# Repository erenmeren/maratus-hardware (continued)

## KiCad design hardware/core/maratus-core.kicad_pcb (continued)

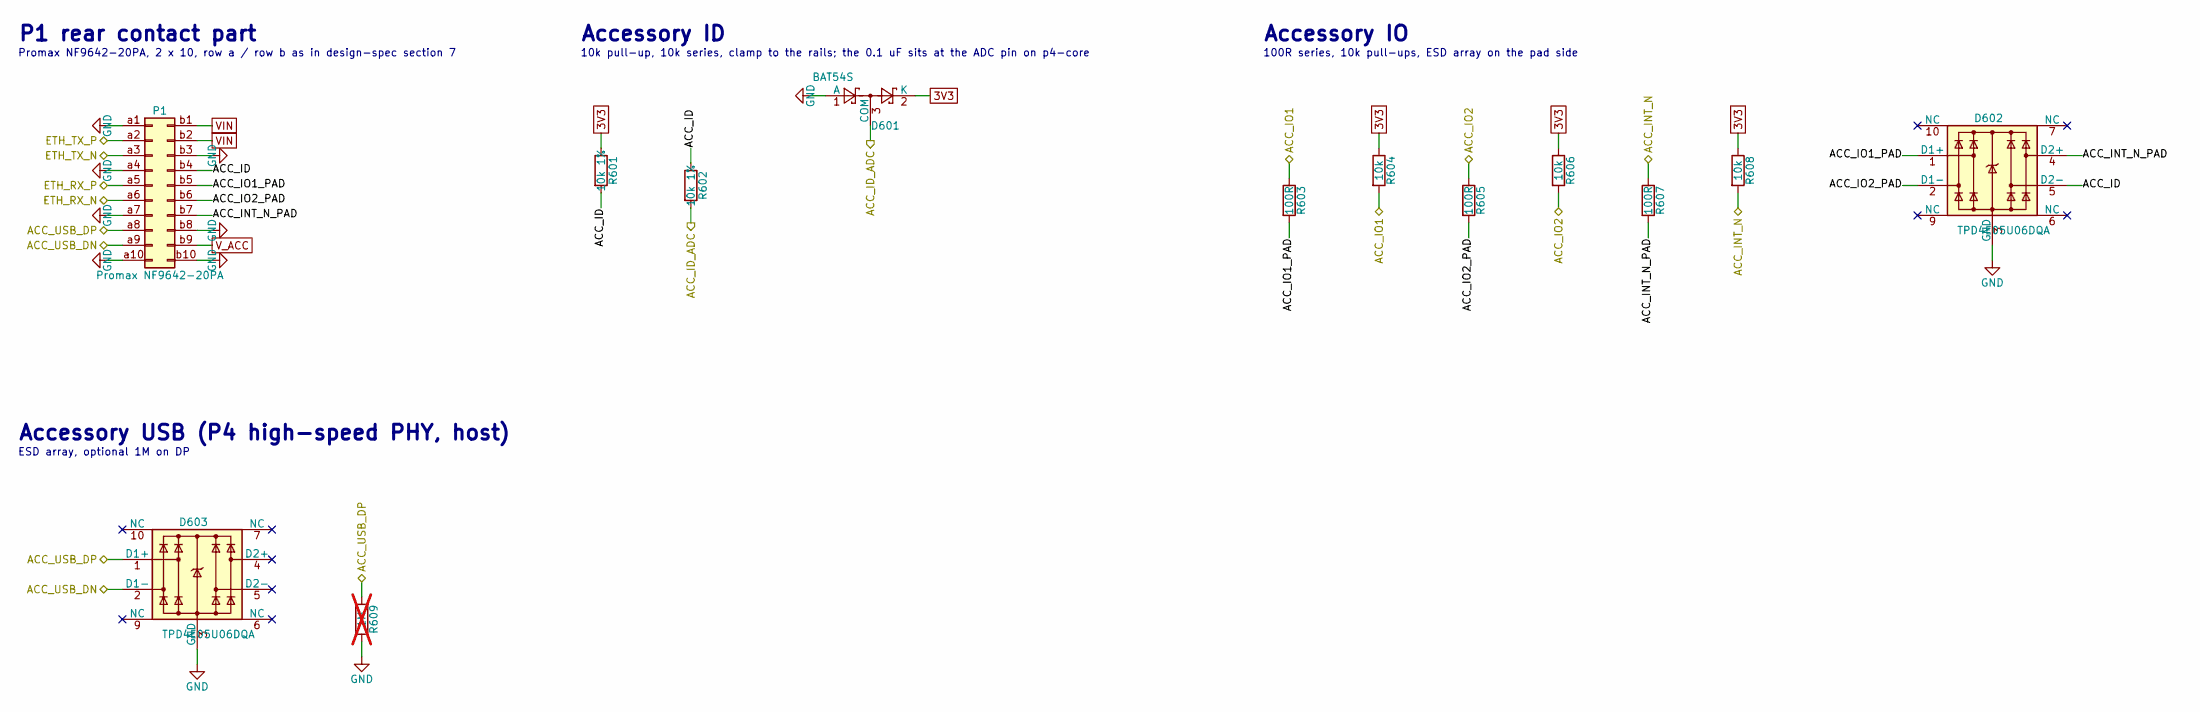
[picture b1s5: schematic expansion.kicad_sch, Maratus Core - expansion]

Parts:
D601: BAT54S; SOT-23
D602, D603: TPD4E05U06DQA; USON-10_2.5x1.0mm_P0.5mm
P1: Promax NF9642-20PA; Promax_NF9642-20PA
R601, R602: 10k 1%; R_0402_1005Metric
R603, R605, R607: 100R; R_0402_1005Metric
R604, R606, R608: 10k; R_0402_1005Metric
R609: 1M; R_0402_1005Metric; not fitted

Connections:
3V3: D601.2 (K), R601.1, R604.1, R606.1, R608.1; also elsewhere on the board
/ACC_ID_ADC: D601.3 (COM), R602.2; also elsewhere on the board
/ACC_INT_N: R607.1, R608.2; also elsewhere on the board
/ACC_IO1: R603.1, R604.2; also elsewhere on the board
/ACC_IO2: R605.1, R606.2; also elsewhere on the board
/ACC_USB_DN: D603.2 (D1-), P1.a9; also elsewhere on the board
/ACC_USB_DP: D603.1 (D1+), P1.a8, R609.1; also elsewhere on the board
/ETH_RX_N: P1.a6; also elsewhere on the board
/ETH_RX_P: P1.a5; also elsewhere on the board
/ETH_TX_N: P1.a3; also elsewhere on the board
/ETH_TX_P: P1.a2; also elsewhere on the board
/expansion/ACC_ID: D602.5 (D2-), P1.b4, R601.2, R602.1
/expansion/ACC_INT_N_PAD: D602.4 (D2+), P1.b7, R607.2
/expansion/ACC_IO1_PAD: D602.1 (D1+), P1.b5, R603.2
/expansion/ACC_IO2_PAD: D602.2 (D1-), P1.b6, R605.2
GND: D601.1 (A), D602.3 (GND), D602.8 (GND), D603.3 (GND), D603.8 (GND), P1.a1, P1.a4, P1.a7, P1.a10, P1.b3, P1.b8, P1.b10, R609.2; also elsewhere on the board
VIN: P1.b1, P1.b2; also elsewhere on the board
V_ACC: P1.b9; also elsewhere on the board

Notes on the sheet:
Accessory USB (P4 high-speed PHY, host)
Accessory ID
P1 rear contact part
Promax NF9642-20PA, 2 x 10, row a / row b as in design-spec section 7
Accessory IO
100R series, 10k pull-ups, ESD array on the pad side
10k pull-up, 10k series, clamp to the rails; the 0.1 uF sits at the ADC pin on p4-core
ESD array, optional 1M on DP

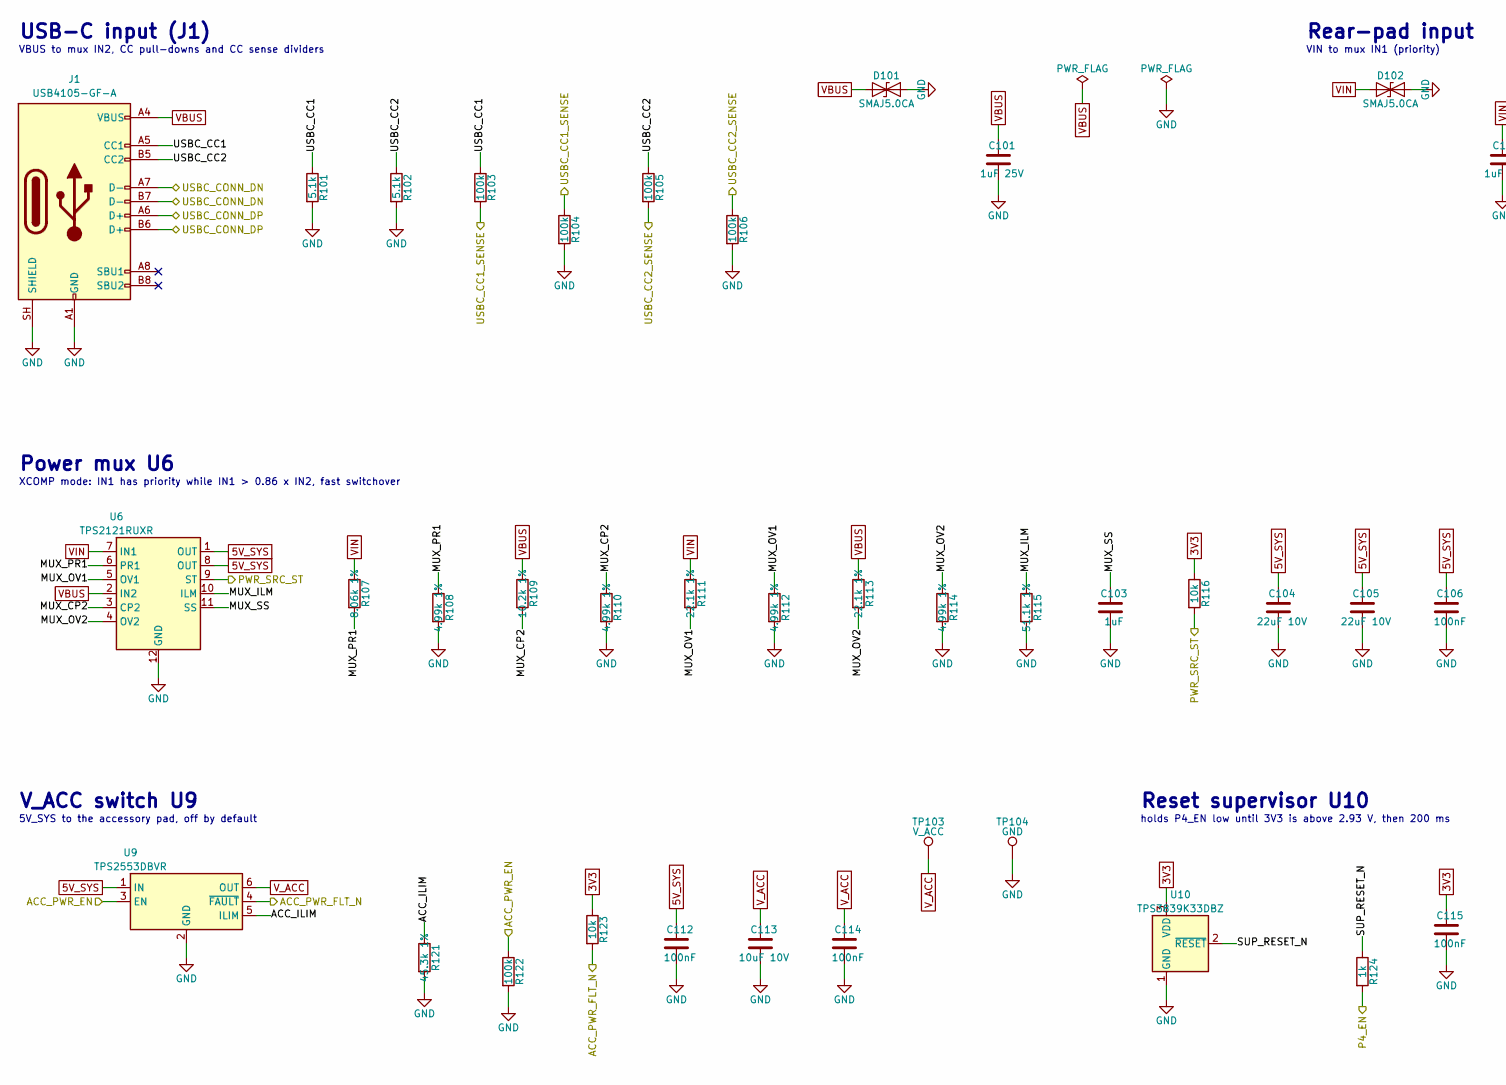
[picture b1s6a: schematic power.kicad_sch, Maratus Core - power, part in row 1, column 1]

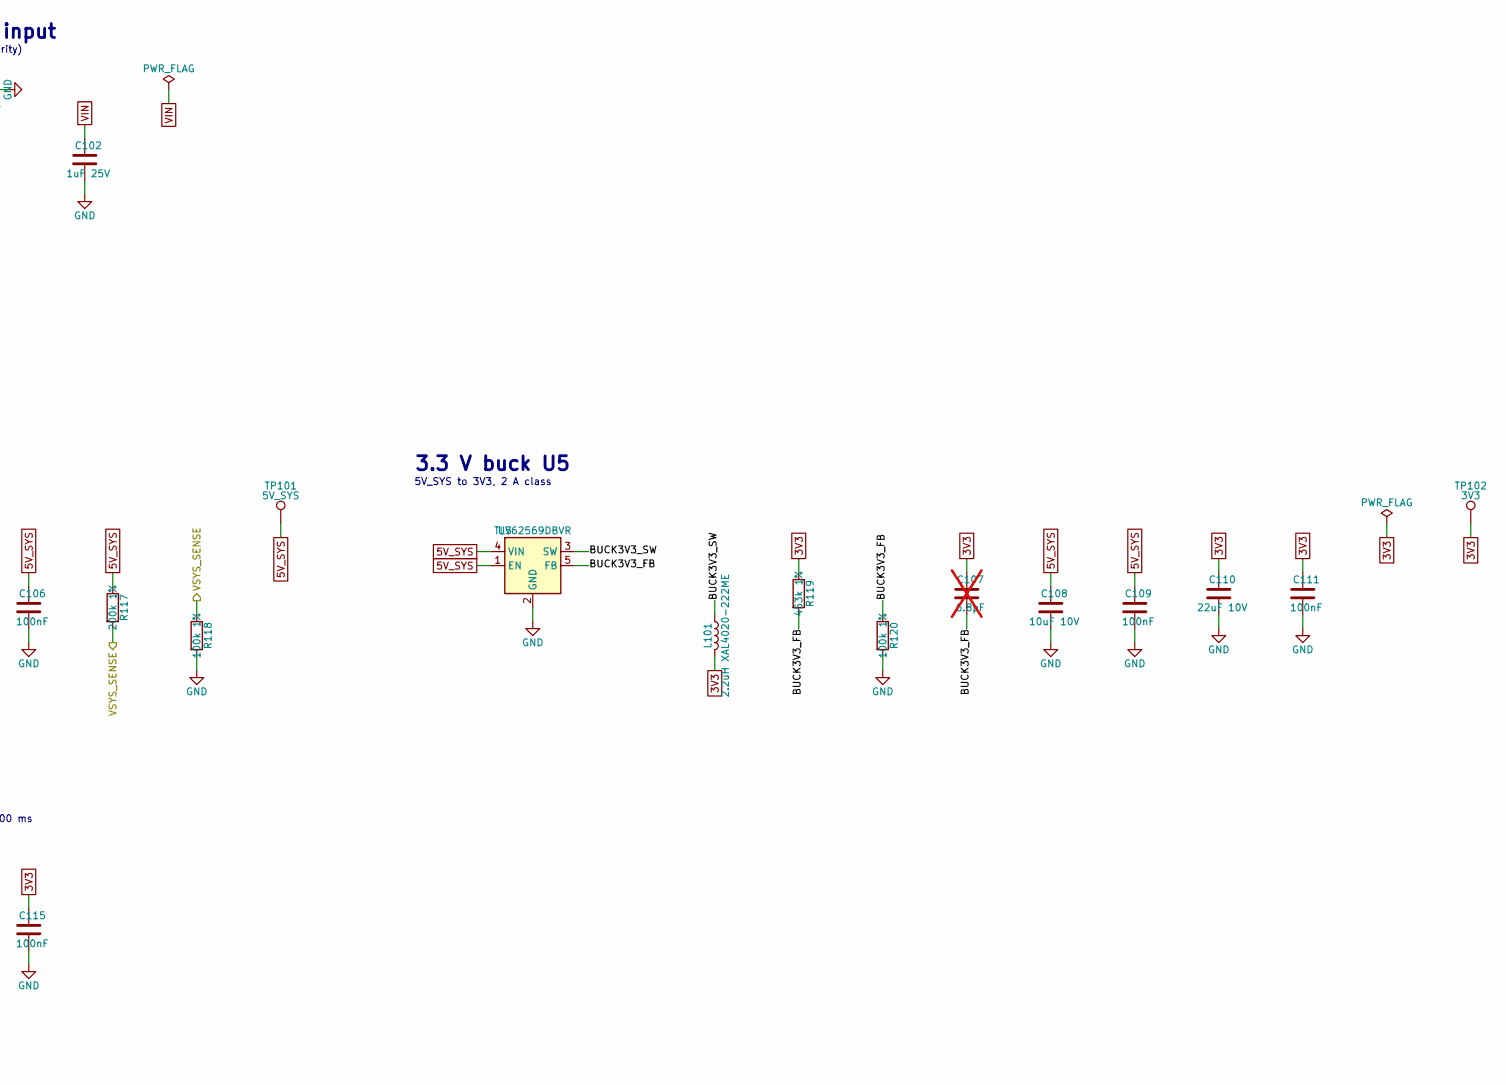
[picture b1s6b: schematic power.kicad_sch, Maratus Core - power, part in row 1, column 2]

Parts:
C101, C102: 1uF 25V; C_0603_1608Metric
C103: 1uF; C_0402_1005Metric
C104, C105, C110: 22uF 10V; C_0805_2012Metric
C106, C109, C111, C112, C114, C115: 100nF; C_0402_1005Metric
C107: 6.8pF; C_0402_1005Metric; not fitted
C108, C113: 10uF 10V; C_0805_2012Metric
D101, D102: SMAJ5.0CA; D_SMA
J1: USB4105-GF-A; USB_C_Receptacle_GCT_USB4105-xx-A_16P_TopMnt_Horizontal
L101: 2.2uH XAL4020-222ME; L_Coilcraft_XAL4020-XXX
R101, R102: 5.1k; R_0402_1005Metric
R103, R104, R105, R106, R122: 100k; R_0402_1005Metric
R107: 8.06k 1%; R_0402_1005Metric
R108, R110, R112, R114: 4.99k 1%; R_0402_1005Metric
R109: 10.2k 1%; R_0402_1005Metric
R111, R113: 22.1k 1%; R_0402_1005Metric
R115: 51.1k 1%; R_0402_1005Metric
R116, R123: 10k; R_0402_1005Metric
R117: 200k 1%; R_0402_1005Metric
R118, R120: 100k 1%; R_0402_1005Metric
R119: 453k 1%; R_0402_1005Metric
R121: 45.3k 1%; R_0402_1005Metric
R124: 1k; R_0402_1005Metric
TP101: 5V_SYS; TestPoint_Pad_D1.0mm
TP102: 3V3; TestPoint_Pad_D1.0mm
TP103: V_ACC; TestPoint_Pad_D1.0mm
TP104: GND; TestPoint_Pad_D1.0mm
U5: TLV62569DBVR; SOT-23-5
U6: TPS2121RUXR; Texas_VQFN-HR-12_2x2.5mm_P0.5mm
U9: TPS2553DBVR; SOT-23-6
U10: TPS3839K33DBZ; SOT-23

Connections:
3V3: C107.1, C110.1, C111.1, C115.1, L101.2, R116.1, R119.1, R123.1, TP102.1, U10.3 (VDD); also elsewhere on the board
5V_SYS: C104.1, C105.1, C106.1, C108.1, C109.1, C112.1, R117.1, TP101.1, U5.1 (EN), U5.4 (VIN), U6.1 (OUT), U6.8 (OUT), U9.1 (IN); also elsewhere on the board
/ACC_PWR_EN: R122.1, U9.3 (EN); also elsewhere on the board
/ACC_PWR_FLT_N: R123.2, U9.4 (~FAULT); also elsewhere on the board
/P4_EN: R124.2; also elsewhere on the board
/PWR_SRC_ST: R116.2, U6.9 (ST); also elsewhere on the board
/USBC_CC1_SENSE: R103.2, R104.1; also elsewhere on the board
/USBC_CC2_SENSE: R105.2, R106.1; also elsewhere on the board
/USBC_CONN_DN: J1.A7 (D-), J1.B7 (D-); also elsewhere on the board
/USBC_CONN_DP: J1.A6 (D+), J1.B6 (D+); also elsewhere on the board
/VSYS_SENSE: R117.2, R118.1; also elsewhere on the board
/power/ACC_ILIM: R121.1, U9.5 (ILIM)
/power/BUCK3V3_FB: C107.2, R119.2, R120.1, U5.5 (FB)
/power/BUCK3V3_SW: L101.1, U5.3 (SW)
/power/MUX_CP2: R109.2, R110.1, U6.3 (CP2)
/power/MUX_ILM: R115.1, U6.10 (ILM)
/power/MUX_OV1: R111.2, R112.1, U6.5 (OV1)
/power/MUX_OV2: R113.2, R114.1, U6.4 (OV2)
/power/MUX_PR1: R107.2, R108.1, U6.6 (PR1)
/power/MUX_SS: C103.1, U6.11 (SS)
/power/SUP_RESET_N: R124.1, U10.2 (~RESET)
/power/USBC_CC1: J1.A5 (CC1), R101.1, R103.1
/power/USBC_CC2: J1.B5 (CC2), R102.1, R105.1
GND: C101.2, C102.2, C103.2, C104.2, C105.2, C106.2, C108.2, C109.2, C110.2, C111.2, C112.2, C113.2, C114.2, C115.2, D101.2 (A2), D102.2 (A2), J1.A1 (GND), J1.A12 (GND), J1.B1 (GND), J1.B12 (GND), J1.SH (SHIELD), R101.2, R102.2, R104.2, R106.2, R108.2, R110.2, R112.2, R114.2, R115.2, R118.2, R120.2, R121.2, R122.2, TP104.1, U5.2 (GND), U6.12 (GND), U9.2 (GND), U10.1 (GND); also elsewhere on the board
VBUS: C101.1, D101.1 (A1), J1.A4 (VBUS), J1.A9 (VBUS), J1.B4 (VBUS), J1.B9 (VBUS), R109.1, R113.1, U6.2 (IN2); also elsewhere on the board
VIN: C102.1, D102.1 (A1), R107.1, R111.1, U6.7 (IN1); also elsewhere on the board
V_ACC: C113.1, C114.1, TP103.1, U9.6 (OUT); also elsewhere on the board

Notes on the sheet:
V_ACC switch U9
5V_SYS to 3V3, 2 A class
3.3 V buck U5
Rear-pad input
5V_SYS to the accessory pad, off by default
VBUS to mux IN2, CC pull-downs and CC sense dividers
USB-C input (J1)
XCOMP mode: IN1 has priority while IN1 > 0.86 x IN2, fast switchover
holds P4_EN low until 3V3 is above 2.93 V, then 200 ms
VIN to mux IN1 (priority)
Power mux U6
Reset supervisor U10

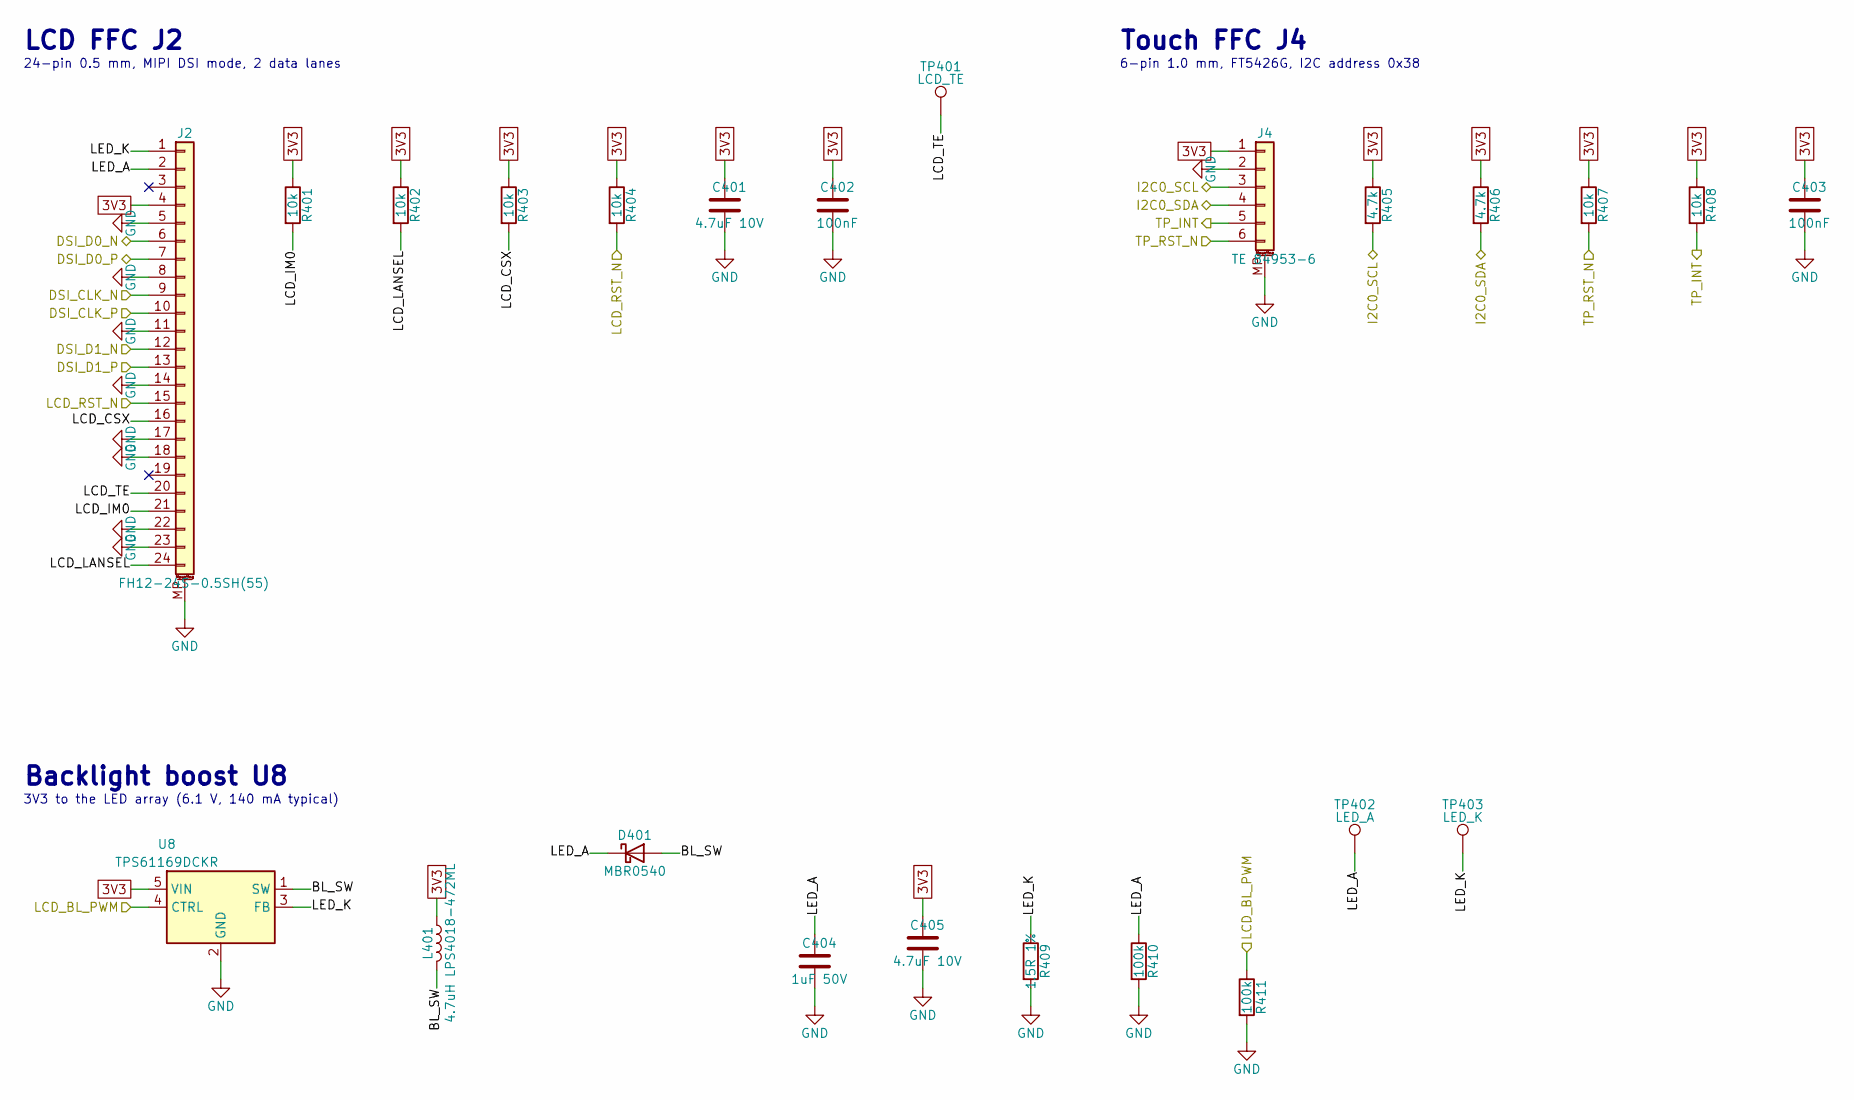
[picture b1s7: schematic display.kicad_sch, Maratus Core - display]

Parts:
C401, C405: 4.7uF 10V; C_0603_1608Metric
C402, C403: 100nF; C_0402_1005Metric
C404: 1uF 50V; C_0805_2012Metric
D401: MBR0540; D_SOD-123
J2: FH12-24S-0.5SH(55); Hirose_FH12-24S-0.5SH_1x24-1MP_P0.50mm_Horizontal
J4: TE 84953-6; TE_84953-6_1x06-1MP_P1.0mm_Horizontal
L401: 4.7uH LPS4018-472ML; L_Coilcraft_LPS4018
R401, R402, R403, R404, R407, R408: 10k; R_0402_1005Metric
R405, R406: 4.7k; R_0402_1005Metric
R409: 1.5R 1%; R_0603_1608Metric
R410, R411: 100k; R_0402_1005Metric
TP401: LCD_TE; TestPoint_Pad_D1.0mm
TP402: LED_A; TestPoint_Pad_D1.0mm
TP403: LED_K; TestPoint_Pad_D1.0mm
U8: TPS61169DCKR; SOT-353_SC-70-5

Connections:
3V3: C401.1, C402.1, C403.1, C405.1, J2.4, J4.1, L401.1, R401.1, R402.1, R403.1, R404.1, R405.1, R406.1, R407.1, R408.1, U8.5 (VIN); also elsewhere on the board
/DSI_CLK_N: J2.9; also elsewhere on the board
/DSI_CLK_P: J2.10; also elsewhere on the board
/DSI_D0_N: J2.6; also elsewhere on the board
/DSI_D0_P: J2.7; also elsewhere on the board
/DSI_D1_N: J2.12; also elsewhere on the board
/DSI_D1_P: J2.13; also elsewhere on the board
/I2C0_SCL: J4.3, R405.2; also elsewhere on the board
/I2C0_SDA: J4.4, R406.2; also elsewhere on the board
/LCD_BL_PWM: R411.1, U8.4 (CTRL); also elsewhere on the board
/LCD_RST_N: J2.15, R404.2; also elsewhere on the board
/TP_INT: J4.5, R408.2; also elsewhere on the board
/TP_RST_N: J4.6, R407.2; also elsewhere on the board
/display/BL_SW: D401.2 (A), L401.2, U8.1 (SW)
/display/LCD_CSX: J2.16, R403.2
/display/LCD_IM0: J2.21, R401.2
/display/LCD_LANSEL: J2.24, R402.2
/display/LCD_TE: J2.20, TP401.1
/display/LED_A: C404.1, D401.1 (K), J2.2, R410.1, TP402.1
/display/LED_K: J2.1, R409.1, TP403.1, U8.3 (FB)
GND: C401.2, C402.2, C403.2, C404.2, C405.2, J2.5, J2.8, J2.11, J2.14, J2.17, J2.18, J2.22, J2.23, J2.MP (MountPin), J4.2, J4.MP (MountPin), R409.2, R410.2, R411.2, U8.2 (GND); also elsewhere on the board

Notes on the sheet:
24-pin 0.5 mm, MIPI DSI mode, 2 data lanes
3V3 to the LED array (6.1 V, 140 mA typical)
6-pin 1.0 mm, FT5426G, I2C address 0x38
LCD FFC J2
Touch FFC J4
Backlight boost U8

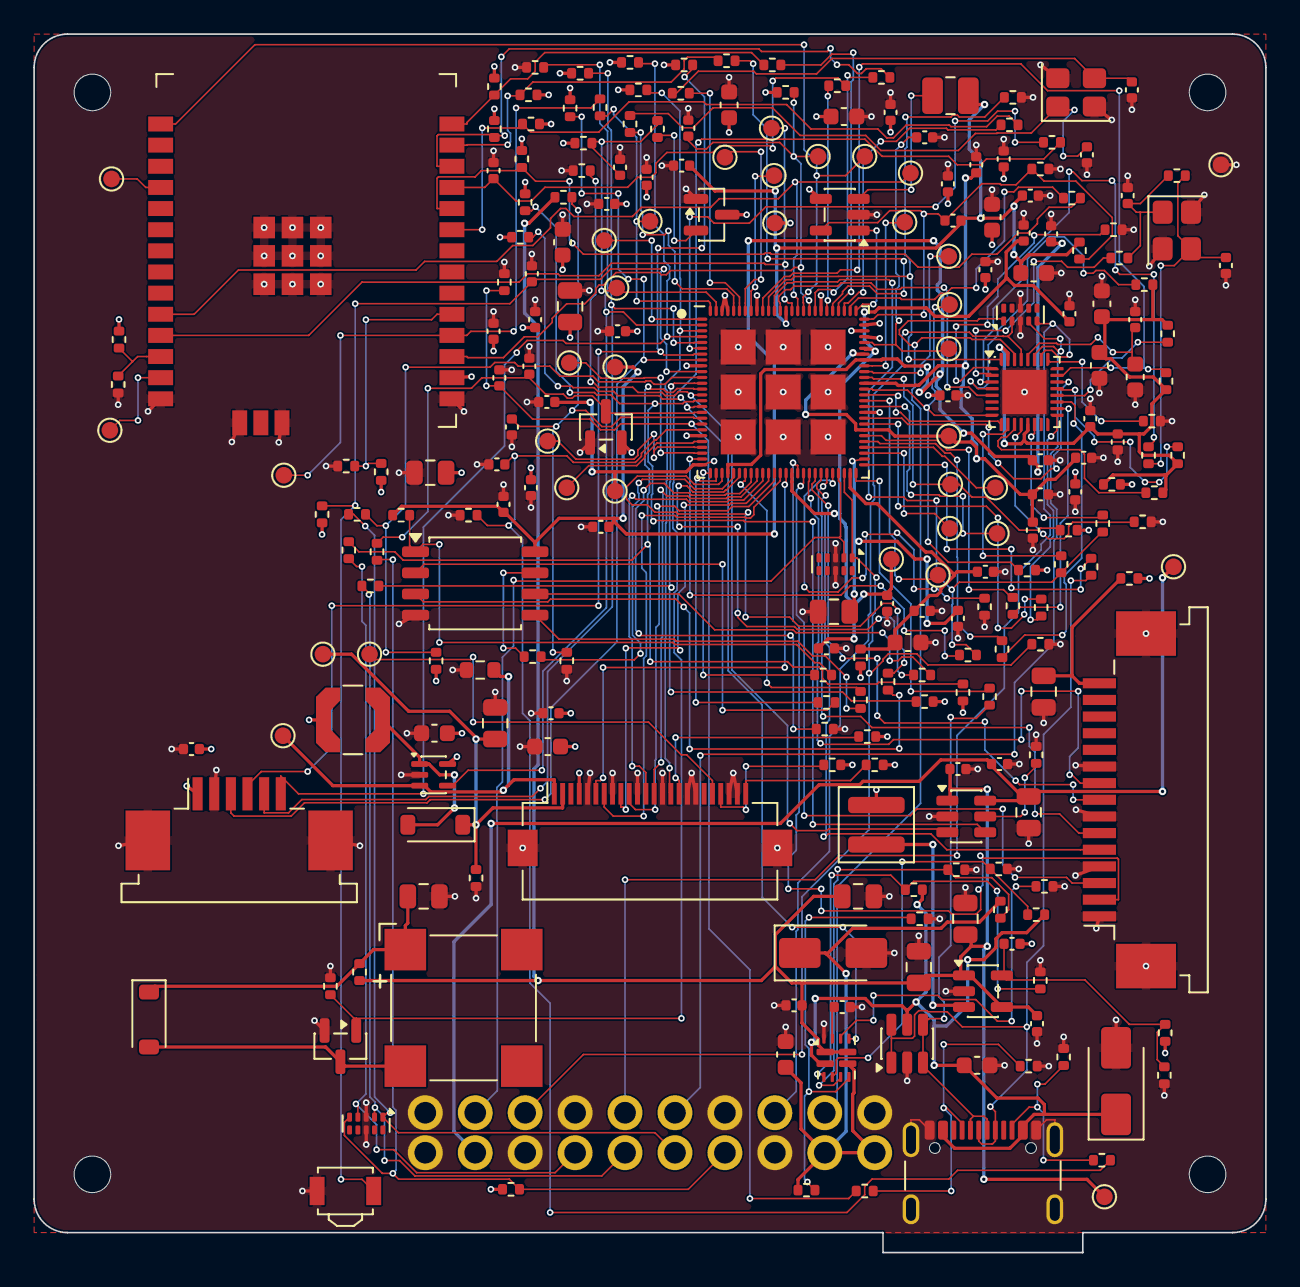
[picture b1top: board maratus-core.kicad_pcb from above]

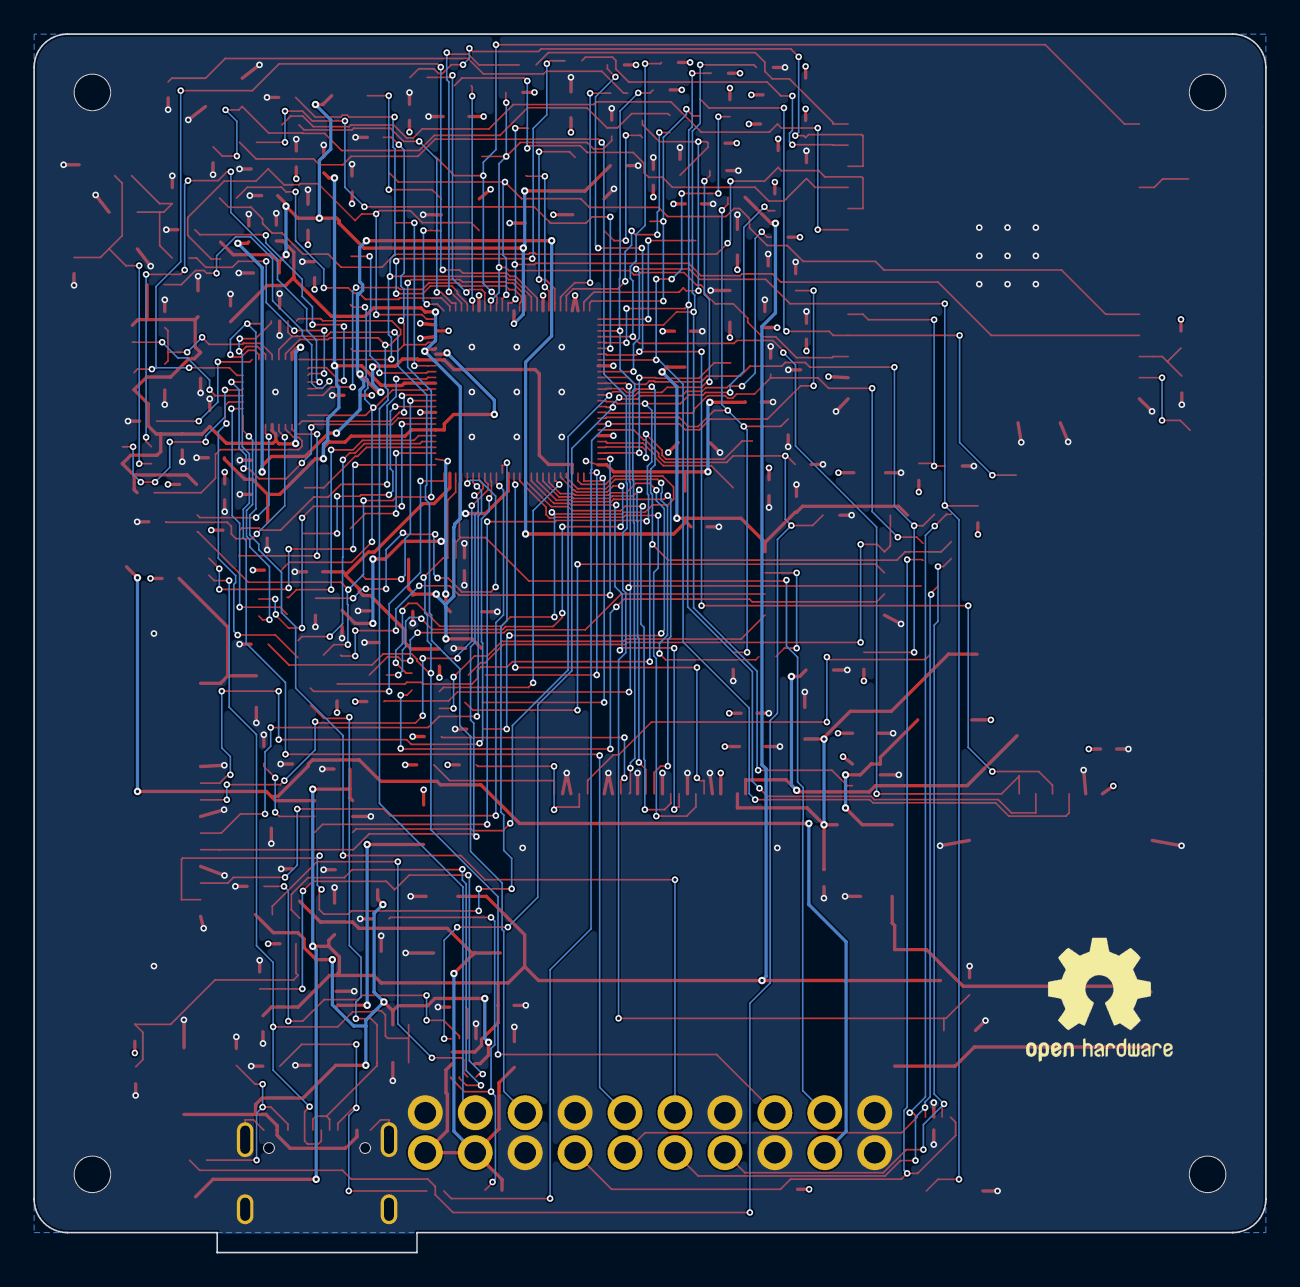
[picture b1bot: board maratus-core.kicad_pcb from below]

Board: 4 copper layers, 74.0 x 73.2 mm, 254 parts (2 on the bottom side), 165 nets.

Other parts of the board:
H1, H2, H3, H4: MountingHole_2.2mm_M2
LOGO1: OSHW-Logo2_9.8x8mm_SilkScreen

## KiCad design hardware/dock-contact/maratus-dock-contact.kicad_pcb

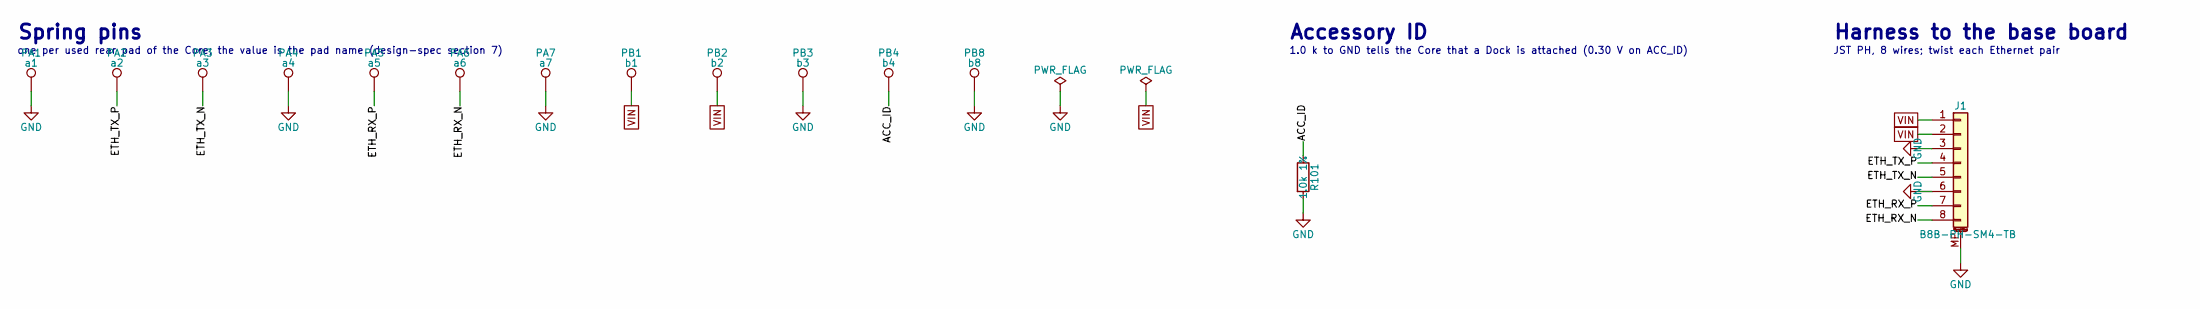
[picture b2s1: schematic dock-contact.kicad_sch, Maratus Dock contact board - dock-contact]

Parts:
J1: B8B-PH-SM4-TB; JST_PH_B8B-PH-SM4-TB_1x08-1MP_P2.00mm_Vertical
PA1: a1; SpringPin_Harwin_P70-2300045R
PA2: a2; SpringPin_Harwin_P70-2300045R
PA3: a3; SpringPin_Harwin_P70-2300045R
PA4: a4; SpringPin_Harwin_P70-2300045R
PA5: a5; SpringPin_Harwin_P70-2300045R
PA6: a6; SpringPin_Harwin_P70-2300045R
PA7: a7; SpringPin_Harwin_P70-2300045R
PB1: b1; SpringPin_Harwin_P70-2300045R
PB2: b2; SpringPin_Harwin_P70-2300045R
PB3: b3; SpringPin_Harwin_P70-2300045R
PB4: b4; SpringPin_Harwin_P70-2300045R
PB8: b8; SpringPin_Harwin_P70-2300045R
R101: 1.0k 1%; R_0402_1005Metric

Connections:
/dock-contact/ACC_ID: PB4.1, R101.1
/dock-contact/ETH_RX_N: J1.8, PA6.1
/dock-contact/ETH_RX_P: J1.7, PA5.1
/dock-contact/ETH_TX_N: J1.5, PA3.1
/dock-contact/ETH_TX_P: J1.4, PA2.1
GND: J1.3, J1.6, J1.MP (MountPin), PA1.1, PA4.1, PA7.1, PB3.1, PB8.1, R101.2
VIN: J1.1, J1.2, PB1.1, PB2.1

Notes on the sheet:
one per used rear pad of the Core; the value is the pad name (design-spec section 7)
1.0 k to GND tells the Core that a Dock is attached (0.30 V on ACC_ID)
Spring pins
Harness to the base board
Accessory ID
JST PH, 8 wires; twist each Ethernet pair

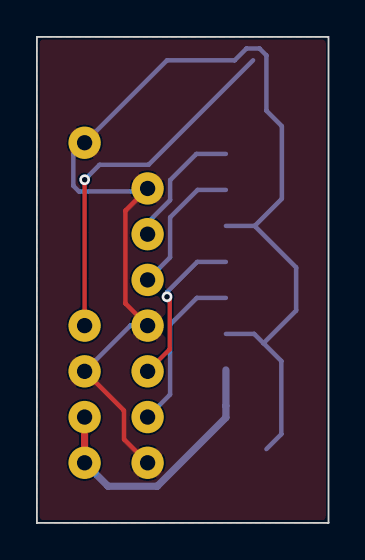
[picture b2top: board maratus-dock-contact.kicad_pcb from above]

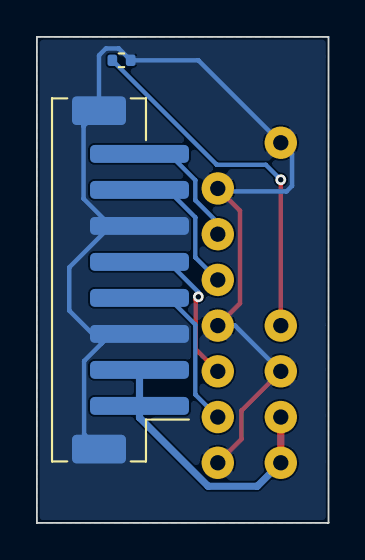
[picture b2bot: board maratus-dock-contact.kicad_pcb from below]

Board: 2 copper layers, 16.2 x 27.0 mm, 14 parts (2 on the bottom side), 7 nets.

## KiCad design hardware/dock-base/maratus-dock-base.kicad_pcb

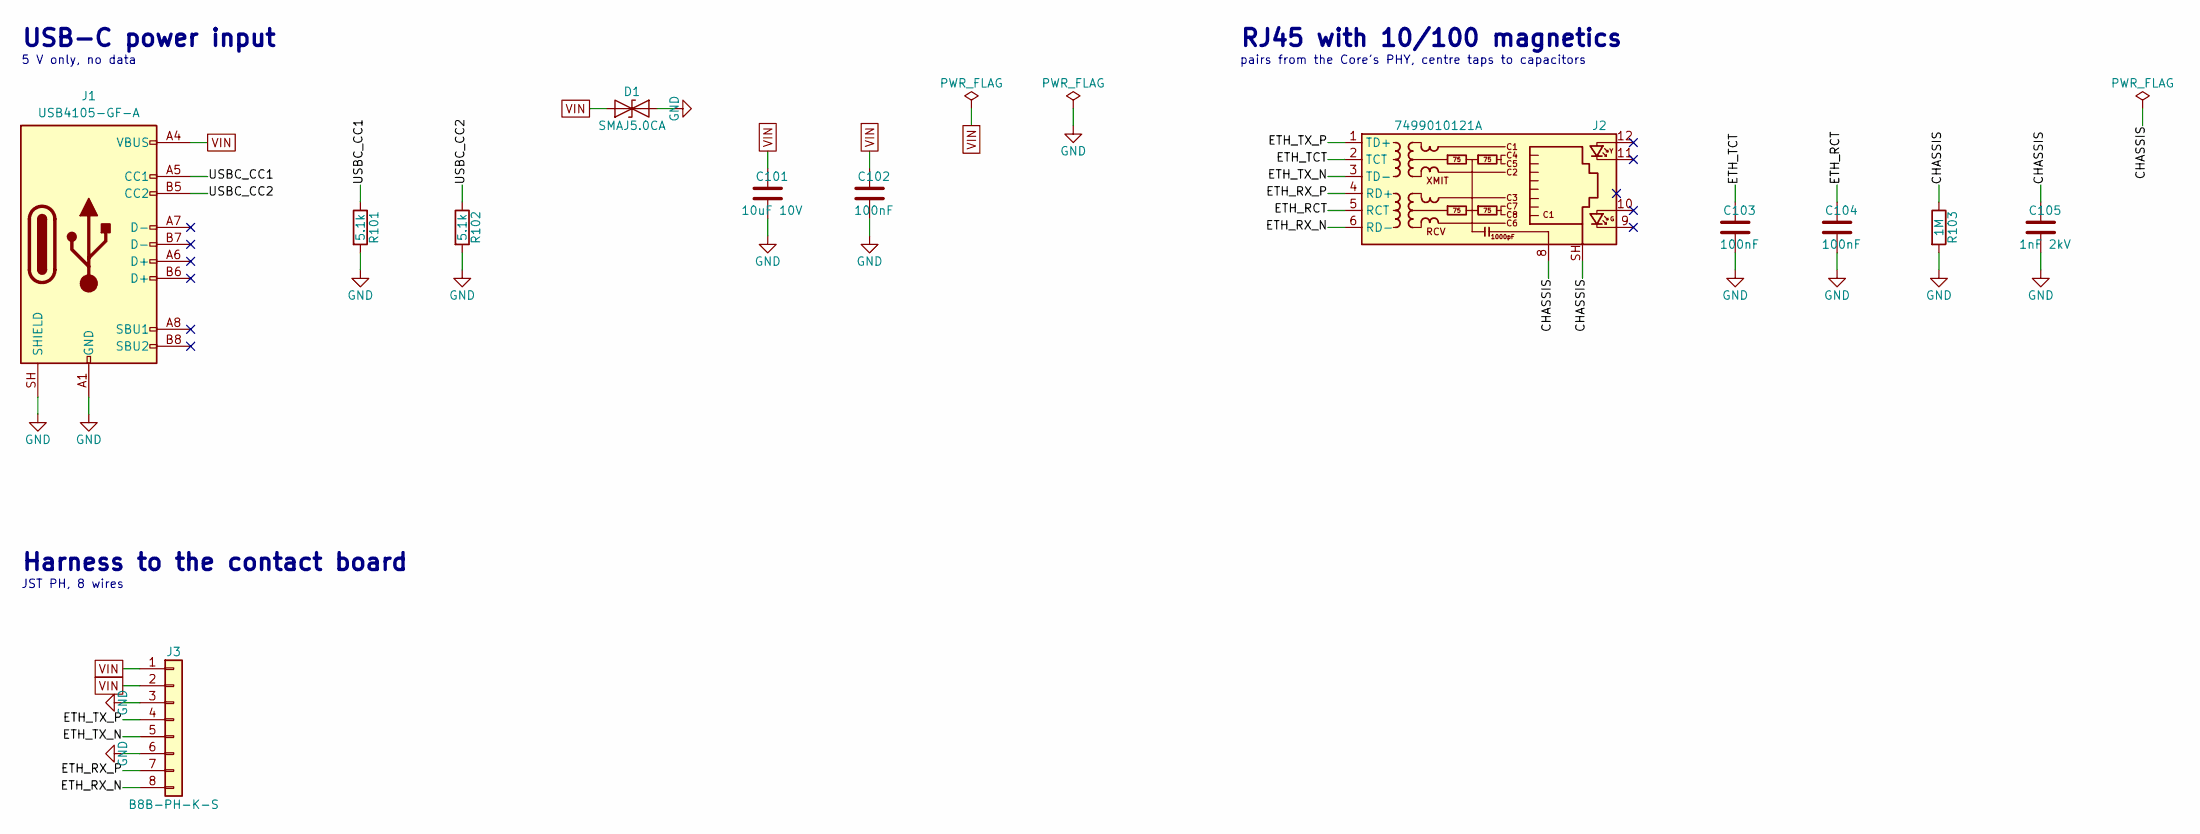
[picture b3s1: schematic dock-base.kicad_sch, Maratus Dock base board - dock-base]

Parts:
C101: 10uF 10V; C_0805_2012Metric
C102, C103, C104: 100nF; C_0402_1005Metric
C105: 1nF 2kV; C_1206_3216Metric
D1: SMAJ5.0CA; D_SMA
J1: USB4105-GF-A; USB_C_Receptacle_GCT_USB4105-xx-A_16P_TopMnt_Horizontal
J2: 7499010121A; RJ45_Wuerth_7499010121A_Horizontal
J3: B8B-PH-K-S; JST_PH_B8B-PH-K_1x08_P2.00mm_Vertical
R101, R102: 5.1k; R_0402_1005Metric
R103: 1M; R_0402_1005Metric

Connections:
/dock-base/CHASSIS: C105.1, J2.8, J2.SH, R103.1
/dock-base/ETH_RCT: C104.1, J2.5 (RCT)
/dock-base/ETH_RX_N: J2.6 (RD-), J3.8
/dock-base/ETH_RX_P: J2.4 (RD+), J3.7
/dock-base/ETH_TCT: C103.1, J2.2 (TCT)
/dock-base/ETH_TX_N: J2.3 (TD-), J3.5
/dock-base/ETH_TX_P: J2.1 (TD+), J3.4
/dock-base/USBC_CC1: J1.A5 (CC1), R101.1
/dock-base/USBC_CC2: J1.B5 (CC2), R102.1
GND: C101.2, C102.2, C103.2, C104.2, C105.2, D1.2 (A2), J1.A1 (GND), J1.A12 (GND), J1.B1 (GND), J1.B12 (GND), J1.SH (SHIELD), J3.3, J3.6, R101.2, R102.2, R103.2
VIN: C101.1, C102.1, D1.1 (A1), J1.A4 (VBUS), J1.A9 (VBUS), J1.B4 (VBUS), J1.B9 (VBUS), J3.1, J3.2

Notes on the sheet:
Harness to the contact board
5 V only, no data
RJ45 with 10/100 magnetics
pairs from the Core's PHY, centre taps to capacitors
USB-C power input
JST PH, 8 wires

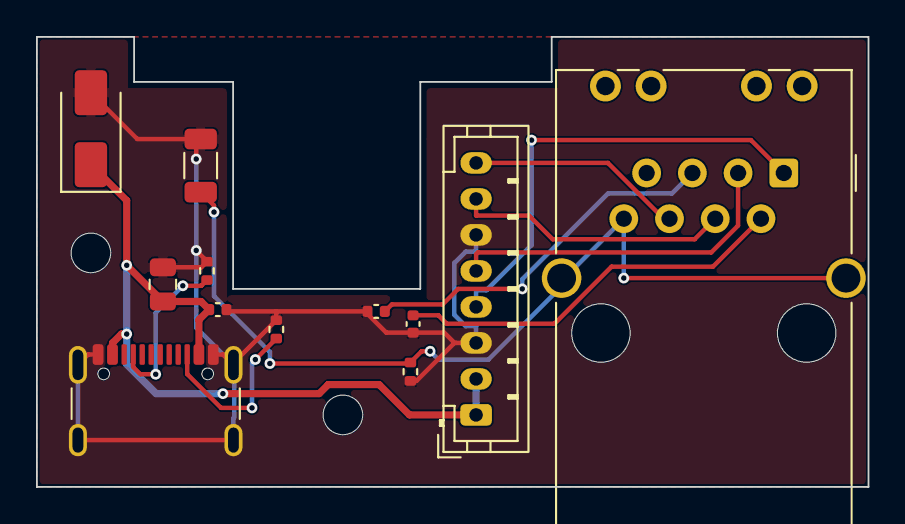
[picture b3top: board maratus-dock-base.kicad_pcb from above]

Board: 2 copper layers, 46.2 x 25.0 mm, 14 parts (0 on the bottom side), 11 nets.

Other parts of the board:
H1, H2: MountingHole_2.2mm_M2

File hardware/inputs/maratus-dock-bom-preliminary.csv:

Ref,Board,Function,Manufacturer,MPN,Package,Qty,Status,Notes
PA1-PA7 PB1-PB4 PB8,dock-contact,Spring pins onto the Core's rear pads,Harwin,P70-2300045R,"Through-hole peg, 1.5 mm body, 6.2 mm free height",12,Candidate,"Working height 4.9 mm, 0.83 N, 2 A, 10,000 cycles. Datasheet in docs/reference."
R101,dock-contact,Accessory ID resistor,any,1.0 k 1%,0402,1,Defined,"Tells the Core a Dock is attached (design-spec section 7)."
J1,dock-contact,Harness header,JST,B8B-PH-SM4-TB,"8-pin, 2.0 mm, SMT top entry",1,Candidate,"Surface mount: no pins may come through this board. jst_ePH.pdf p.4."
J1,dock-base,USB-C receptacle (power only),GCT,USB4105-GF-A,16-pin SMT,1,Candidate,"Same part as the Core's J1. CC1/CC2 5.1 k to GND."
J2,dock-base,RJ45 jack with 10/100 magnetics,Wurth Elektronik,7499010121A,"Through-hole, 16.1 x 25.4 x 13.55 mm",1,Candidate,"1:1, centre taps on pins 2 and 5. Position over the board edge is an assumption. Datasheet in docs/reference."
J3,dock-base,Harness header,JST,B8B-PH-K-S,"8-pin, 2.0 mm, through-hole top entry",1,Candidate,"jst_ePH.pdf p.3."
D1,dock-base,5 V input TVS,Vishay,SMAJ5.0CA,SMA,1,Candidate,"Same part as on the Core."
R101-R102,dock-base,USB-C CC pull-downs,any,5.1 k,0402,2,Defined,
R103,dock-base,Shield bleed resistor,any,1 M,0402,1,Assumption,"Jack shield to GND. For EMC review."
C101,dock-base,Input bulk capacitor,any,10 uF 10 V,0805,1,Assumption,
C102-C104,dock-base,Input and centre-tap capacitors,any,100 nF,0402,3,Defined,"Centre taps to capacitors only (IP101G datasheet p.7)."
C105,dock-base,Shield capacitor,any,1 nF 2 kV,1206,1,Assumption,"Jack shield to GND. For EMC review."
-,harness,Housing,JST,PHR-8,8-pin,2,Candidate,"jst_ePH.pdf p.3."
-,harness,Crimp contact,JST,SPH-002T-P0.5S,AWG 30-24,16,Candidate,"jst_ePH.pdf p.2. AWG 24 wire, Ethernet pairs twisted."
-,mechanical,Printed saddle (both bodies),-,mechanical/dock/maratus-dock-saddle.stl,20.8 x 27.2 x 6.9 mm,1,Prototype,"Holds the contact board from the front; carries the block for the Core's pad window."
-,mechanical,Printed port drawer (both bodies),-,mechanical/dock/maratus-dock-drawer.stl,49.2 x 18.0 x 20.0 mm,1,Prototype,"Port panel with the shelf for the base board."
-,mechanical,Saddle screw,any,M2 x 8 thread-forming countersunk,-,2,Defined,
-,mechanical,Base board screw,any,M2 x 4 thread-forming,-,2,Defined,"Board onto the drawer's shelf. Pan head. The hole is 3.3 mm deep under a 1.6 mm board."
-,mechanical,Magnets,supermagnete,S-10-02-N,"10 x 2 mm disc, N42, Ni-Cu-Ni",4,Candidate,"Two stacks of two, glued into the Dock's front. The same part as in the Core. Pull is calculated, not measured."
-,mechanical,Lock screw,any,M2 x 8 thread-forming,-,2,Defined,"Optional lock since the magnets. Dock to Core. BAR: the Core's outer bosses; FLOAT: the inner bosses."
-,mechanical BAR,Printed body,-,mechanical/dock-bar/body.stl,77.0 x 37.1 x 36.5 mm,1,Prototype,"Supports inside when printed standing on one end."
-,mechanical BAR,Printed end caps (left and right),-,mechanical/dock-bar/cap-left.stl and cap-right.stl,4.2 x 35.1 x 36.5 mm,2,Prototype,"Orange. Glue in: no press fit designed."
-,mechanical BAR,Drawer screw,any,M2 x 10 thread-forming countersunk,-,1,Defined,"From below through the bar."
-,mechanical BAR,Mounting tape,-,-,70 x 8.5 mm,1,Assumption,"The bar tips at a light push without it (design-spec section 13)."
-,mechanical FLOAT,Printed pod,-,mechanical/dock-float/pod.stl,59.0 x 45.4 x 39.2 mm,1,Prototype,"Open at the top: the cap closes it."
-,mechanical FLOAT,Printed cap,-,mechanical/dock-float/cap.stl,58.3 x 34.9 x 22.1 mm,1,Prototype,"The wedge's slope and rear roll. Lifts off for the lock screws; held by its fit only, not tuned."
-,mechanical FLOAT,Printed plate,-,mechanical/dock-float/plate.stl,81.4 x 66.0 x 3.0 mm,1,Prototype,"Orange. A 3 mm steel plate of this outline (about 123 g) would stand better; not designed."
-,mechanical FLOAT,Plate screw,any,M2 x 8 thread-forming countersunk,-,4,Defined,"Plate to pod."
-,mechanical FLOAT,Drawer screw,any,M2 x 6 thread-forming countersunk,-,2,Defined,"Through the plate into the drawer's shelf."
